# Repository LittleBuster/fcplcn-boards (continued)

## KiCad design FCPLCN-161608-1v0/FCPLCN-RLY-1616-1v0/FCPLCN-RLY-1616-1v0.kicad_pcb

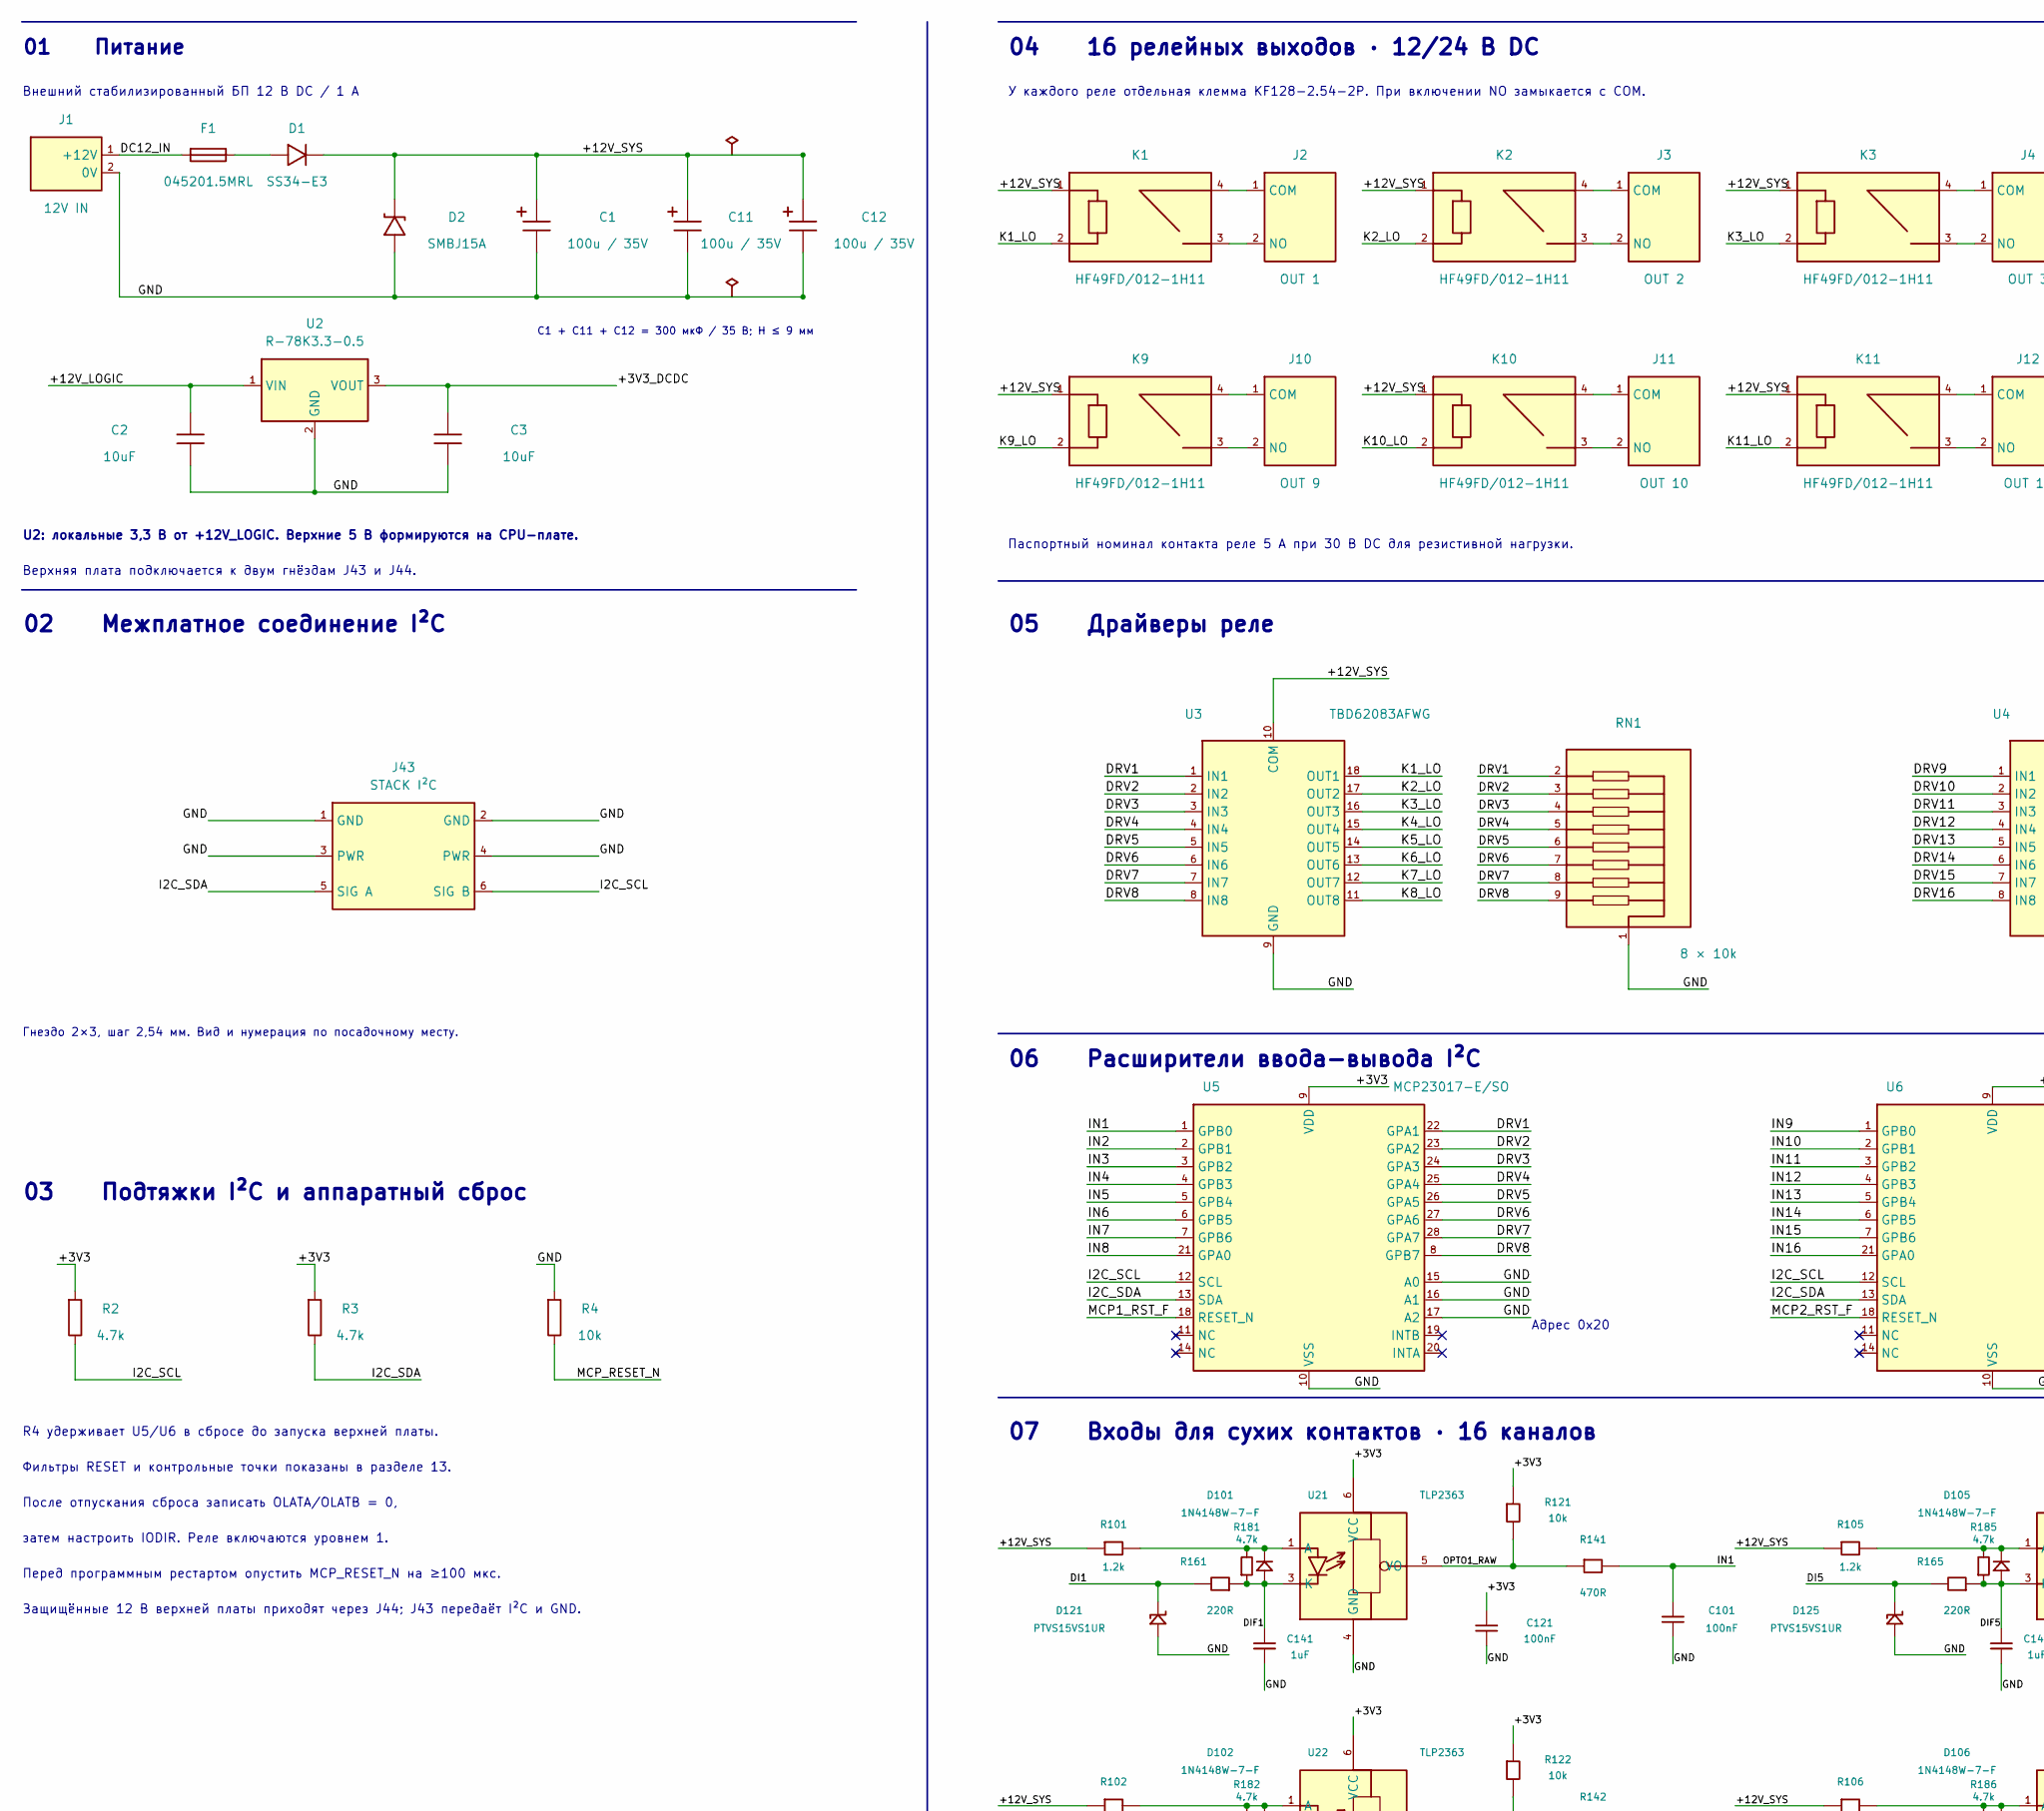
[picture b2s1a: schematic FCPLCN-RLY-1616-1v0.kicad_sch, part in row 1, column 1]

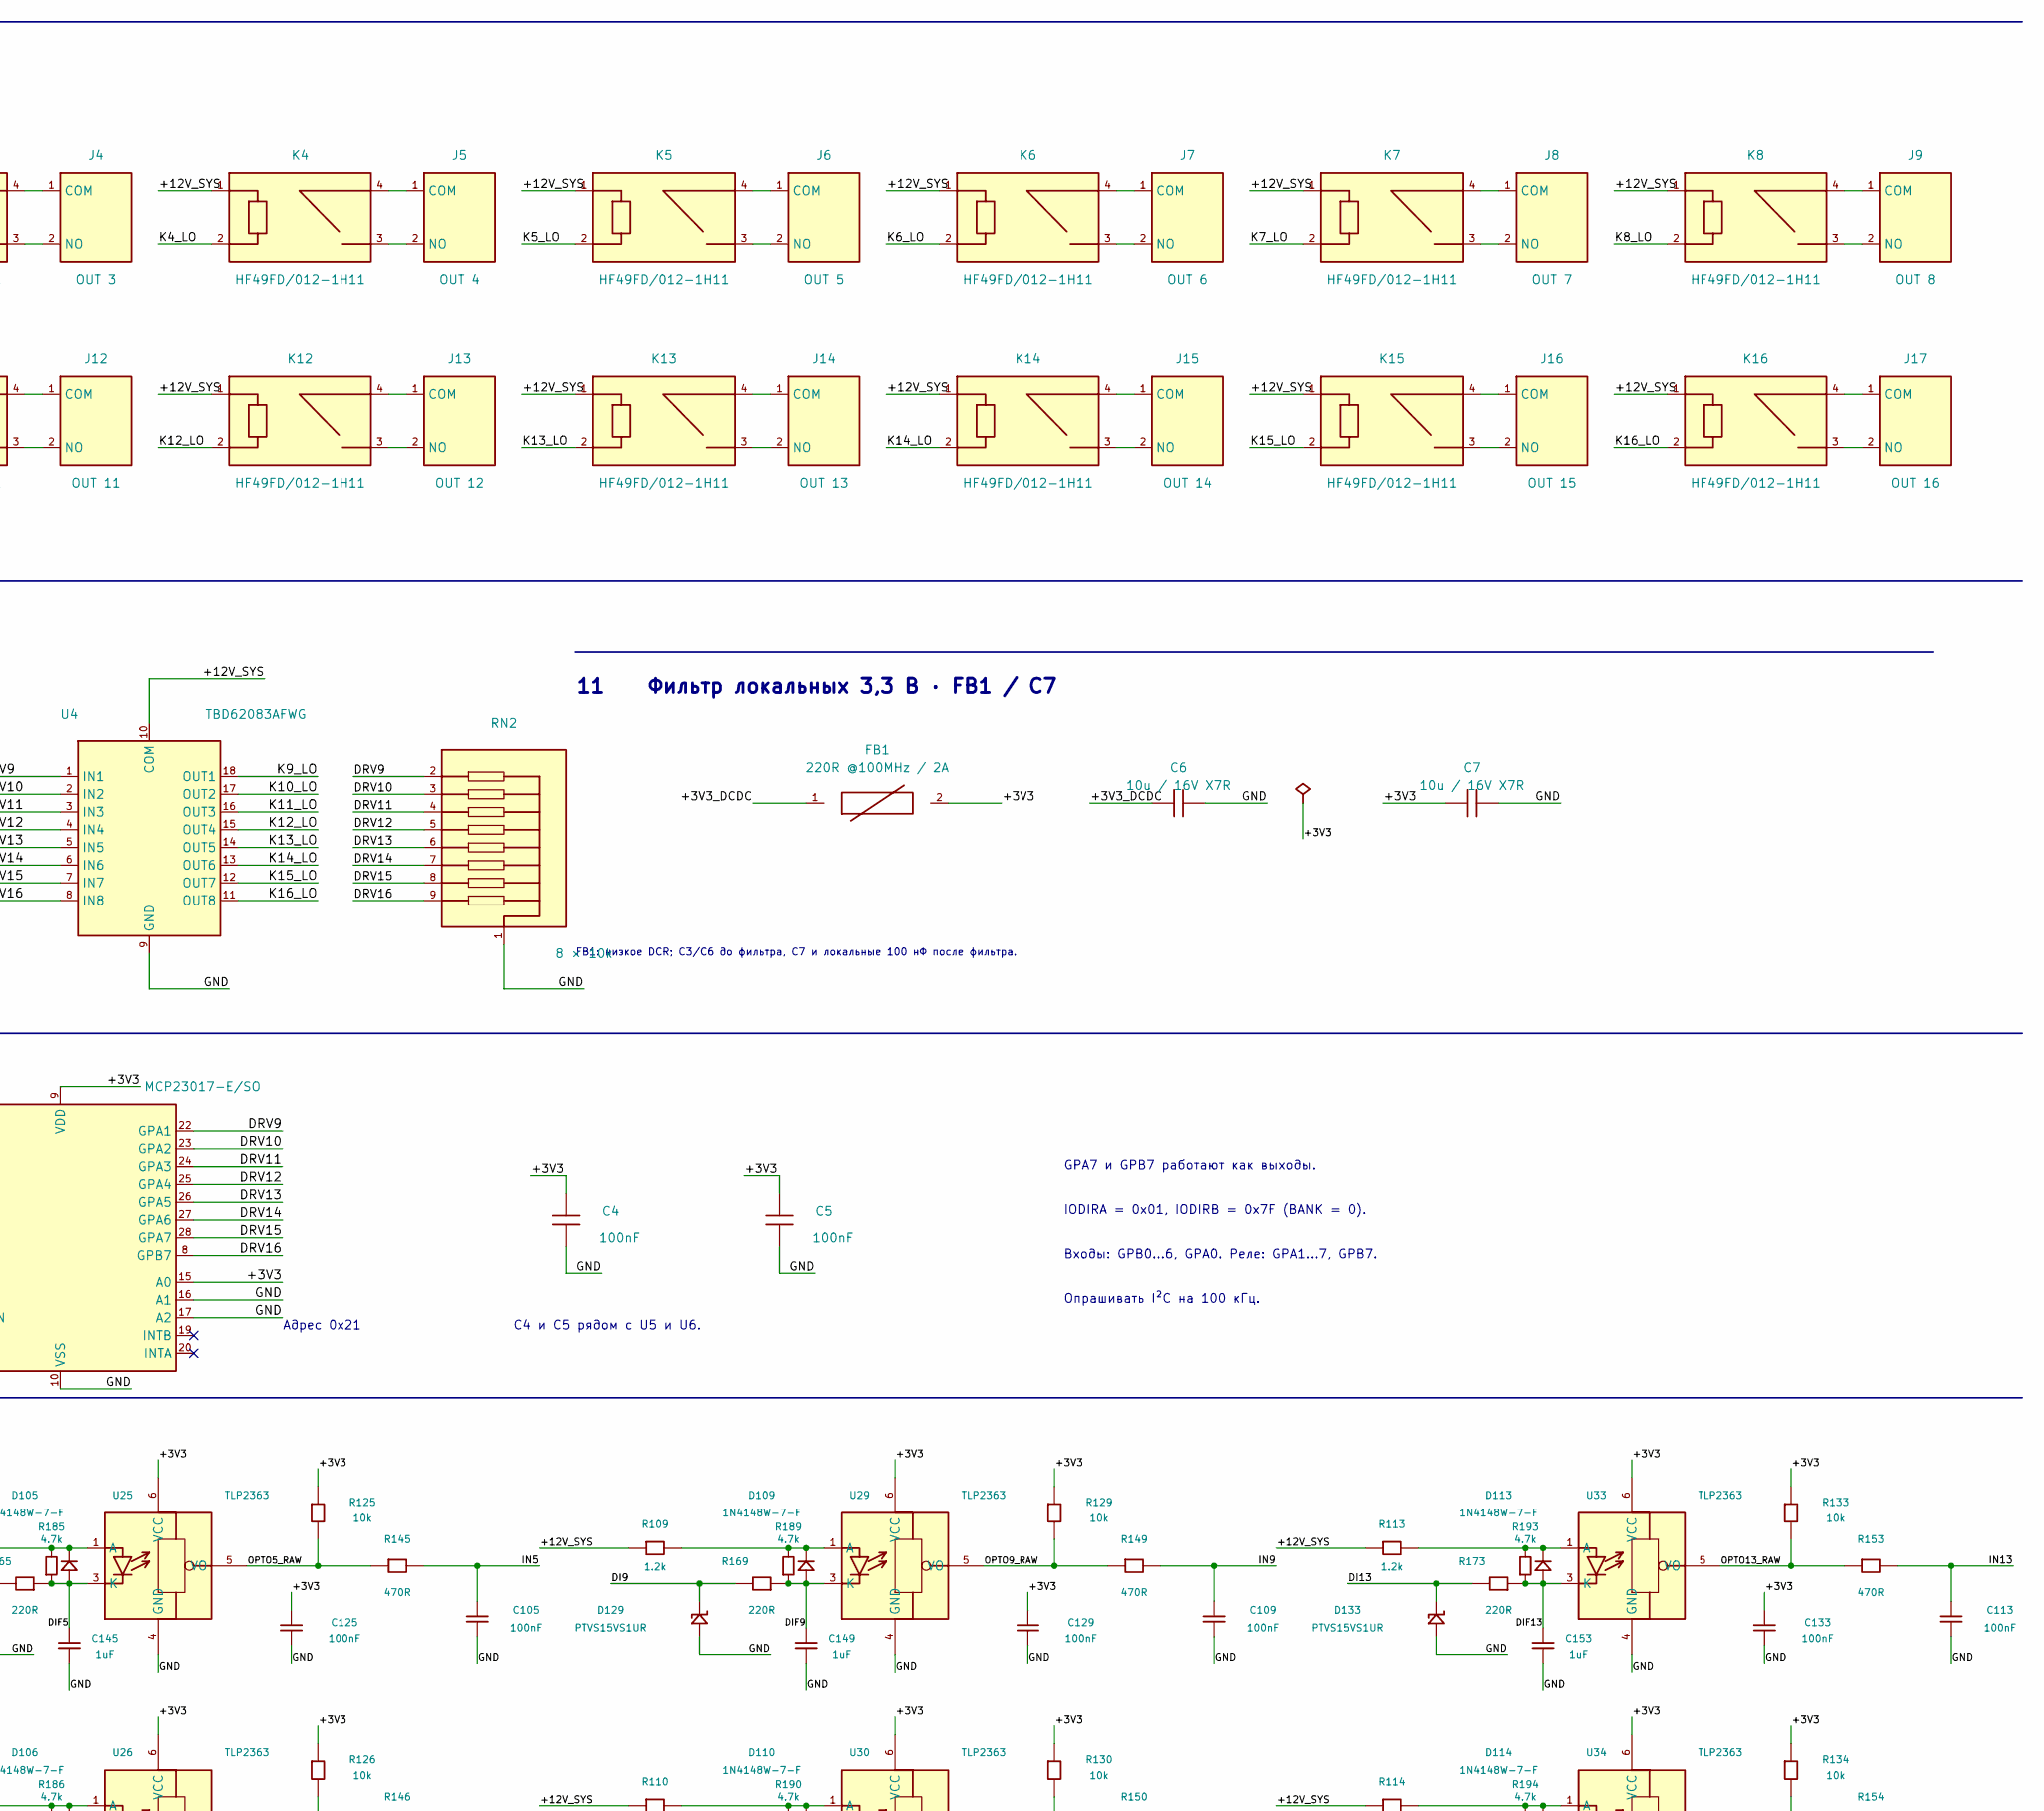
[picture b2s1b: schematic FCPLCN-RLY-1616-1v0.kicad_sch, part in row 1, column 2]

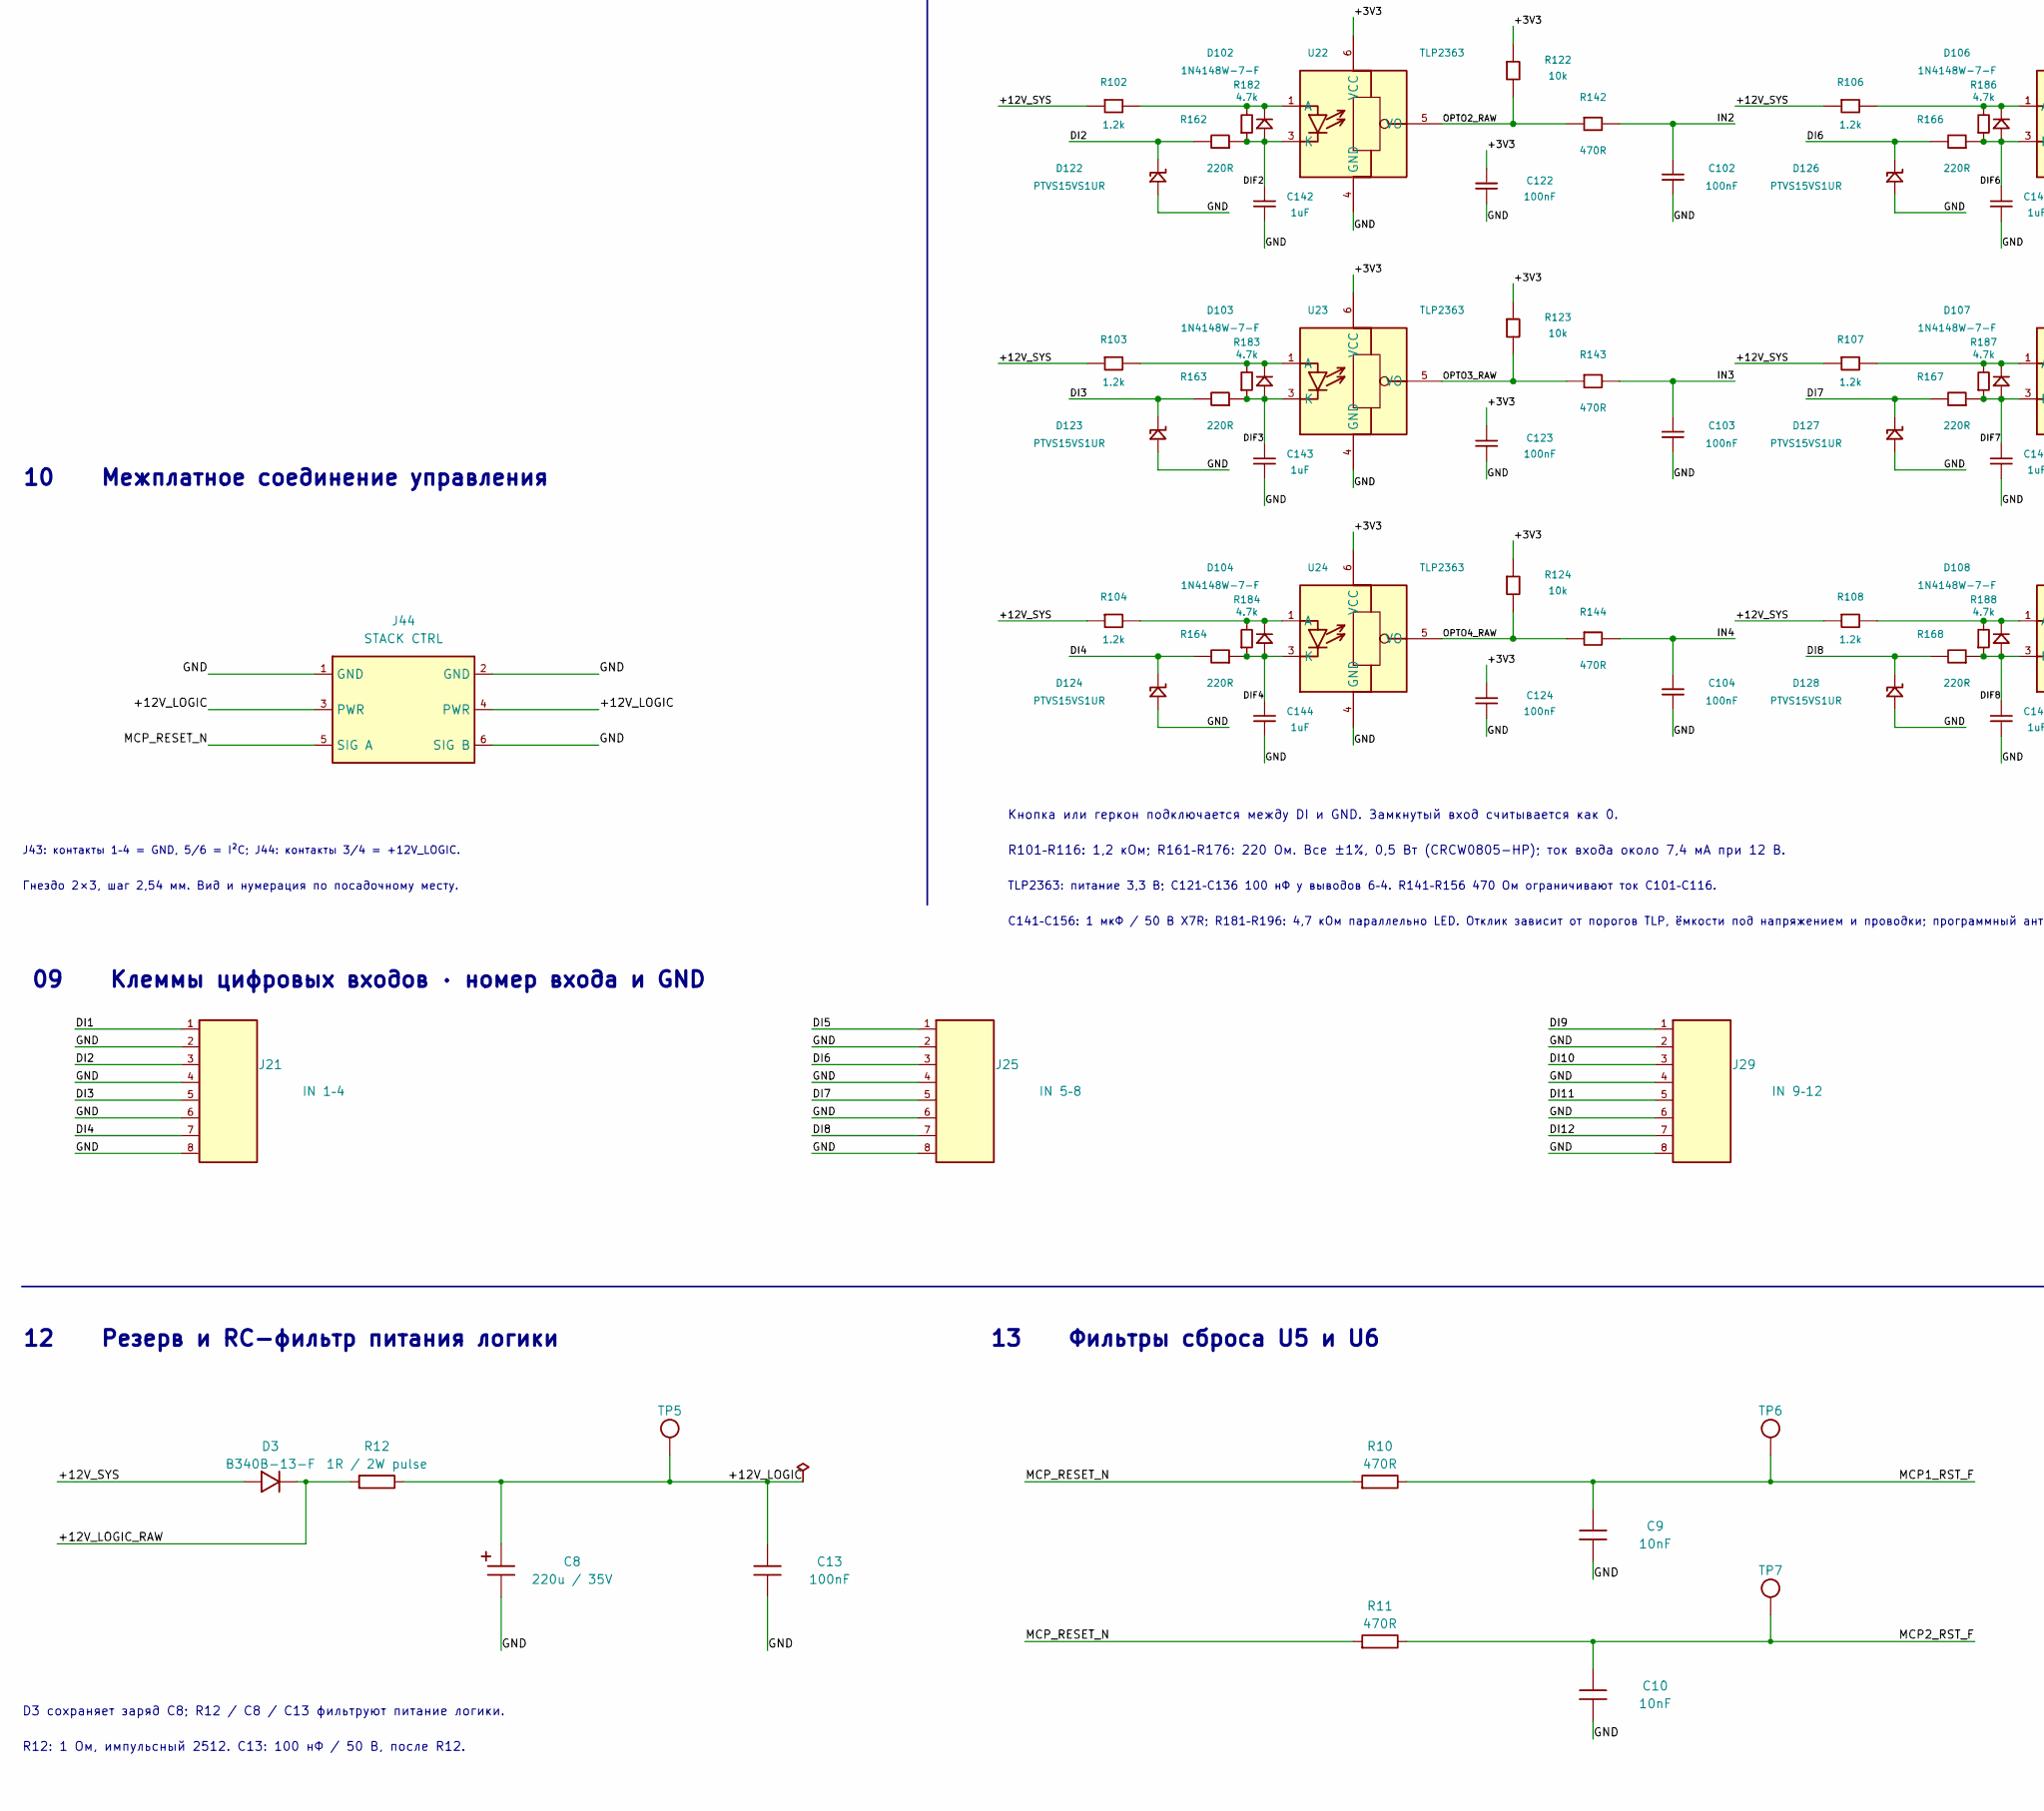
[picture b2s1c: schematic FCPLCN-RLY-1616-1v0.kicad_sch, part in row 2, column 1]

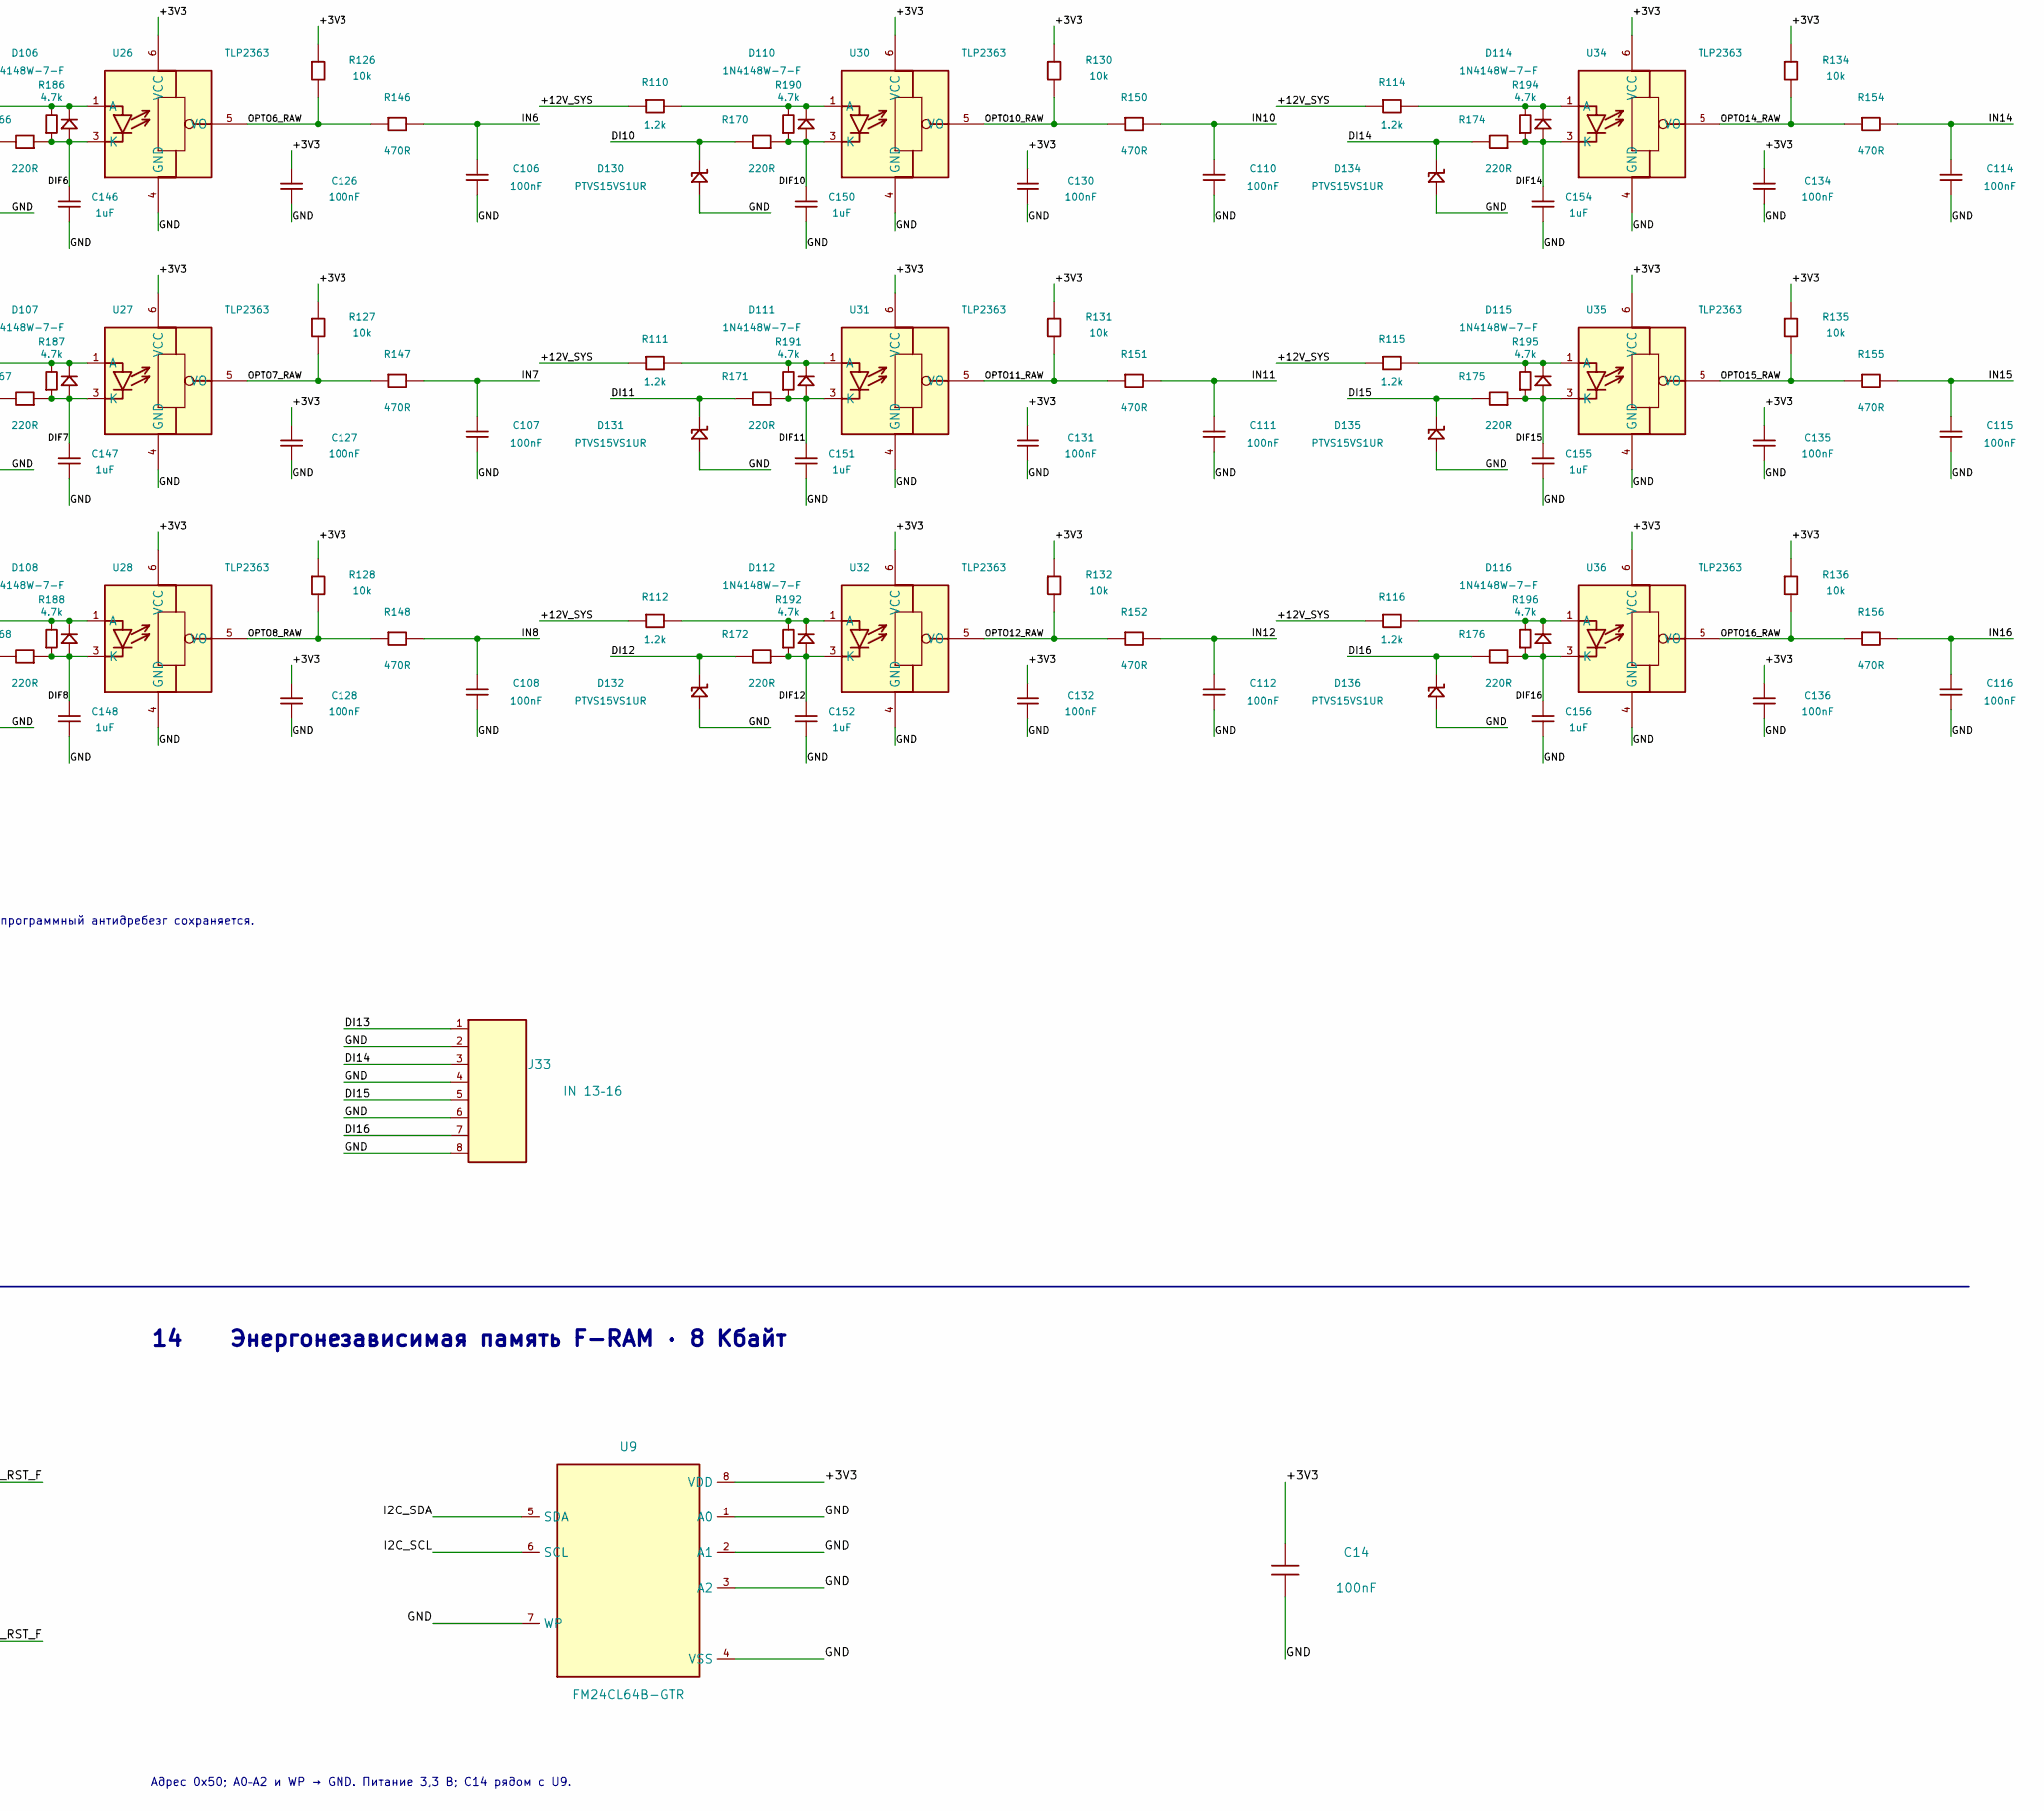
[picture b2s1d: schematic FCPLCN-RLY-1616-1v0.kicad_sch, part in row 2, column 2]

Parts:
C1, C11, C12: 100u / 35V; CP_APAQ_ARHA_D6.3mm_P2.5mm_H9max; Tolerance 20%; MPN 350ARHA101M06X8P00
C2, C3: 10uF; C_1206_3216Metric; Tolerance 10%; Voltage 35 V; MPN C3216X7R1V106K160AC
C4, C5, C14, C101, C102, C103, C104, C105, C106, C107, C108, C109, C110, C111, C112, C113, C114, C115, C116, C121, C122, C123, C124, C125, C126, C127, C128, C129, C130, C131, C132, C133, C134, C135, C136: 100nF; C_0805_2012Metric; Tolerance 10%; Voltage 50 V
C6, C7: 10u / 16V X7R; C_0805_2012Metric
C8: 220u / 35V; CP_Radial_D8.0mm_P3.50mm
C9, C10: 10nF; C_0805_2012Metric; Tolerance 10%; Voltage 50 V
C13: 100nF; C_0805_2012Metric; Voltage 50 V; Tolerance 10%
C141, C142, C143, C144, C145, C146, C147, C148, C149, C150, C151, C152, C153, C154, C155, C156: 1uF; C_0805_2012Metric; Tolerance 10%; Voltage 50 V; MPN C2012X7R1H105K125AB
D1: SS34-E3; D_SMC
D2: SMBJ15A; D_SMB
D3: B340B-13-F; D_SMB
D101, D102, D103, D104, D105, D106, D107, D108, D109, D110, D111, D112, D113, D114, D115, D116: 1N4148W-7-F; D_SOD-123
D121, D122, D123, D124, D125, D126, D127, D128, D129, D130, D131, D132, D133, D134, D135, D136: PTVS15VS1UR; Nexperia_CFP3_SOD-123W
F1: 045201.5MRL; Fuse_Littelfuse-NANO2-451_453; MPN 045201.5MRL
FB1: 220R @100MHz / 2A; L_0805_PowerFilter; MPN BLM21PG221SN1D
J1: 12V IN; KF128-2.54-2P
J2: OUT 1; KF128-2.54-2P
J3: OUT 2; KF128-2.54-2P
J4: OUT 3; KF128-2.54-2P
J5: OUT 4; KF128-2.54-2P
J6: OUT 5; KF128-2.54-2P
J7: OUT 6; KF128-2.54-2P
J8: OUT 7; KF128-2.54-2P
J9: OUT 8; KF128-2.54-2P
J10: OUT 9; KF128-2.54-2P
J11: OUT 10; KF128-2.54-2P
J12: OUT 11; KF128-2.54-2P
J13: OUT 12; KF128-2.54-2P
J14: OUT 13; KF128-2.54-2P
J15: OUT 14; KF128-2.54-2P
J16: OUT 15; KF128-2.54-2P
J17: OUT 16; KF128-2.54-2P
J21: IN 1–4; KF128-2.54-8P
J25: IN 5–8; KF128-2.54-8P
J29: IN 9–12; KF128-2.54-8P
J33: IN 13–16; KF128-2.54-8P
J43: STACK I²C; StackSocket_2x03_P2.54mm; MPN SSW-103-01-L-D
J44: STACK CTRL; StackSocket_2x03_P2.54mm; MPN SSW-103-01-L-D
K1, K2, K3, K4, K5, K6, K7, K8, K9, K10, K11, K12, K13, K14, K15, K16: HF49FD/012-1H11; Relay_SPST_Hongfa_HF49FD-1H11
R2, R3, R181, R182, R183, R184, R185, R186, R187, R188, R189, R190, R191, R192, R193, R194, R195, R196: 4.7k; R_0805_2012Metric; Tolerance 1%
R4, R121, R122, R123, R124, R125, R126, R127, R128, R129, R130, R131, R132, R133, R134, R135, R136: 10k; R_0805_2012Metric; Tolerance 1%
R10, R11, R141, R142, R143, R144, R145, R146, R147, R148, R149, R150, R151, R152, R153, R154, R155, R156: 470R; R_0805_2012Metric; Tolerance 1%
R12: 1R / 2W pulse; R_2512_6332Metric; Tolerance 1%; Voltage_Drop_Design 0.55 V at simultaneous design budget; MPN CRM2512-FX-1R00ELF
R101, R102, R103, R104, R105, R106, R107, R108, R109, R110, R111, R112, R113, R114, R115, R116: 1.2k; R_0805_Wetting; Tolerance 1%; MPN CRCW08051K20FKTAHP
R161, R162, R163, R164, R165, R166, R167, R168, R169, R170, R171, R172, R173, R174, R175, R176: 220R; R_0805_2012Metric; Tolerance 1%; MPN CRCW0805220RFKTAHP
RN1, RN2: 8 × 10k; R_Array_SIP9
TP5, TP6, TP7: TP; TestPoint_Pad_D1.5mm
U2: R-78K3.3-0.5; RECOM_R-78K3.3-0.5_SIP3_P2.54mm; MPN R-78K3.3-0.5
U3, U4: TBD62083AFWG; SOP-18_7.495x11.515mm_P1.27mm
U5, U6: MCP23017-E/SO; SOIC-28W_7.5x17.9mm_P1.27mm
U9: FM24CL64B-GTR; SOIC-8_3.9x4.9mm_P1.27mm; MPN FM24CL64B-GTR
U21, U22, U23, U24, U25, U26, U27, U28, U29, U30, U31, U32, U33, U34, U35, U36: TLP2363; TLP2363_5pin_SO6; MPN TLP2363(TPL,E

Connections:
/+3V3: C4.1, C5.1, C7.1, C14.1, C121.1, C122.1, C123.1, C124.1, C125.1, C126.1, C127.1, C128.1, C129.1, C130.1, C131.1, C132.1, C133.1, C134.1, C135.1, C136.1, FB1.2, R2.1, R3.1, R121.1, R122.1, R123.1, R124.1, R125.1, R126.1, R127.1, R128.1, R129.1, R130.1, R131.1, R132.1, R133.1, R134.1, R135.1, R136.1, U5.9 (VDD), U6.9 (VDD), U6.15 (A0), U9.8 (VDD), U21.6 (VCC), U22.6 (VCC), U23.6 (VCC), U24.6 (VCC), U25.6 (VCC), U26.6 (VCC), U27.6 (VCC), U28.6 (VCC), U29.6 (VCC), U30.6 (VCC), U31.6 (VCC), U32.6 (VCC), U33.6 (VCC), U34.6 (VCC), U35.6 (VCC), U36.6 (VCC)
/+3V3_DCDC: C3.1, C6.1, FB1.1, U2.3 (VOUT)
/+12V_LOGIC: C2.1, C8.1 (+), C13.1, J44.3 (PWR), J44.4 (PWR), R12.2, TP5.1, U2.1 (VIN)
/+12V_LOGIC_RAW: D3.1 (K), R12.1
/+12V_SYS: C1.1 (+), C11.1 (+), C12.1 (+), D1.1 (K), D2.1 (K), D3.2 (A), K1.1 (COIL), K2.1 (COIL), K3.1 (COIL), K4.1 (COIL), K5.1 (COIL), K6.1 (COIL), K7.1 (COIL), K8.1 (COIL), K9.1 (COIL), K10.1 (COIL), K11.1 (COIL), K12.1 (COIL), K13.1 (COIL), K14.1 (COIL), K15.1 (COIL), K16.1 (COIL), R101.1, R102.1, R103.1, R104.1, R105.1, R106.1, R107.1, R108.1, R109.1, R110.1, R111.1, R112.1, R113.1, R114.1, R115.1, R116.1, U3.10 (COM), U4.10 (COM)
/DC12_IN: F1.1, J1.1 (+12V)
/DI1: D121.1 (K), J21.1, R161.2
/DI2: D122.1 (K), J21.3, R162.2
/DI3: D123.1 (K), J21.5, R163.2
/DI4: D124.1 (K), J21.7, R164.2
/DI5: D125.1 (K), J25.1, R165.2
/DI6: D126.1 (K), J25.3, R166.2
/DI7: D127.1 (K), J25.5, R167.2
/DI8: D128.1 (K), J25.7, R168.2
/DI9: D129.1 (K), J29.1, R169.2
/DI10: D130.1 (K), J29.3, R170.2
/DI11: D131.1 (K), J29.5, R171.2
/DI12: D132.1 (K), J29.7, R172.2
/DI13: D133.1 (K), J33.1, R173.2
/DI14: D134.1 (K), J33.3, R174.2
/DI15: D135.1 (K), J33.5, R175.2
/DI16: D136.1 (K), J33.7, R176.2
/DIF1: C141.1, D101.2 (A), R161.1, R181.2, U21.3 (K)
/DIF2: C142.1, D102.2 (A), R162.1, R182.2, U22.3 (K)
/DIF3: C143.1, D103.2 (A), R163.1, R183.2, U23.3 (K)
/DIF4: C144.1, D104.2 (A), R164.1, R184.2, U24.3 (K)
/DIF5: C145.1, D105.2 (A), R165.1, R185.2, U25.3 (K)
/DIF6: C146.1, D106.2 (A), R166.1, R186.2, U26.3 (K)
/DIF7: C147.1, D107.2 (A), R167.1, R187.2, U27.3 (K)
/DIF8: C148.1, D108.2 (A), R168.1, R188.2, U28.3 (K)
/DIF9: C149.1, D109.2 (A), R169.1, R189.2, U29.3 (K)
/DIF10: C150.1, D110.2 (A), R170.1, R190.2, U30.3 (K)
/DIF11: C151.1, D111.2 (A), R171.1, R191.2, U31.3 (K)
/DIF12: C152.1, D112.2 (A), R172.1, R192.2, U32.3 (K)
/DIF13: C153.1, D113.2 (A), R173.1, R193.2, U33.3 (K)
/DIF14: C154.1, D114.2 (A), R174.1, R194.2, U34.3 (K)
/DIF15: C155.1, D115.2 (A), R175.1, R195.2, U35.3 (K)
/DIF16: C156.1, D116.2 (A), R176.1, R196.2, U36.3 (K)
/DRV1: RN1.2, U3.1 (IN1), U5.22 (GPA1)
/DRV2: RN1.3, U3.2 (IN2), U5.23 (GPA2)
/DRV3: RN1.4, U3.3 (IN3), U5.24 (GPA3)
/DRV4: RN1.5, U3.4 (IN4), U5.25 (GPA4)
/DRV5: RN1.6, U3.5 (IN5), U5.26 (GPA5)
/DRV6: RN1.7, U3.6 (IN6), U5.27 (GPA6)
/DRV7: RN1.8, U3.7 (IN7), U5.28 (GPA7)
/DRV8: RN1.9, U3.8 (IN8), U5.8 (GPB7)
/DRV9: RN2.2, U4.1 (IN1), U6.22 (GPA1)
/DRV10: RN2.3, U4.2 (IN2), U6.23 (GPA2)
/DRV11: RN2.4, U4.3 (IN3), U6.24 (GPA3)
/DRV12: RN2.5, U4.4 (IN4), U6.25 (GPA4)
/DRV13: RN2.6, U4.5 (IN5), U6.26 (GPA5)
/DRV14: RN2.7, U4.6 (IN6), U6.27 (GPA6)
/DRV15: RN2.8, U4.7 (IN7), U6.28 (GPA7)
/DRV16: RN2.9, U4.8 (IN8), U6.8 (GPB7)
/GND: C1.2 (-), C2.2, C3.2, C4.2, C5.2, C6.2, C7.2, C8.2 (-), C9.2, C10.2, C11.2 (-), C12.2 (-), C13.2, C14.2, C101.2, C102.2, C103.2, C104.2, C105.2, C106.2, C107.2, C108.2, C109.2, C110.2, C111.2, C112.2, C113.2, C114.2, C115.2, C116.2, C121.2, C122.2, C123.2, C124.2, C125.2, C126.2, C127.2, C128.2, C129.2, C130.2, C131.2, C132.2, C133.2, C134.2, C135.2, C136.2, C141.2, C142.2, C143.2, C144.2, C145.2, C146.2, C147.2, C148.2, C149.2, C150.2, C151.2, C152.2, C153.2, C154.2, C155.2, C156.2, D2.2 (A), D121.2 (A), D122.2 (A), D123.2 (A), D124.2 (A), D125.2 (A), D126.2 (A), D127.2 (A), D128.2 (A), D129.2 (A), D130.2 (A), D131.2 (A), D132.2 (A), D133.2 (A), D134.2 (A), D135.2 (A), D136.2 (A), J1.2 (0V), J21.2, J21.4, J21.6, J21.8, J25.2, J25.4, J25.6, J25.8, J29.2, J29.4, J29.6, J29.8, J33.2, J33.4, J33.6, J33.8, J43.1 (GND), J43.2 (GND), J43.3 (PWR), J43.4 (PWR), J44.1 (GND), J44.2 (GND), J44.6 (SIG B), R4.1, RN1.1 (COM), RN2.1 (COM), U2.2 (GND), U3.9 (GND), U4.9 (GND), U5.10 (VSS), U5.15 (A0), U5.16 (A1), U5.17 (A2), U6.10 (VSS), U6.16 (A1), U6.17 (A2), U9.1 (A0), U9.2 (A1), U9.3 (A2), U9.4 (VSS), U9.7 (WP), U21.4 (GND), U22.4 (GND), U23.4 (GND), U24.4 (GND), U25.4 (GND), U26.4 (GND), U27.4 (GND), U28.4 (GND), U29.4 (GND), U30.4 (GND), U31.4 (GND), U32.4 (GND), U33.4 (GND), U34.4 (GND), U35.4 (GND), U36.4 (GND)
/I2C_SCL: J43.6 (SIG B), R2.2, U5.12 (SCL), U6.12 (SCL), U9.6 (SCL)
/I2C_SDA: J43.5 (SIG A), R3.2, U5.13 (SDA), U6.13 (SDA), U9.5 (SDA)
/IN1: C101.1, R141.2, U5.1 (GPB0)
/IN2: C102.1, R142.2, U5.2 (GPB1)
/IN3: C103.1, R143.2, U5.3 (GPB2)
/IN4: C104.1, R144.2, U5.4 (GPB3)
/IN5: C105.1, R145.2, U5.5 (GPB4)
/IN6: C106.1, R146.2, U5.6 (GPB5)
/IN7: C107.1, R147.2, U5.7 (GPB6)
/IN8: C108.1, R148.2, U5.21 (GPA0)
/IN9: C109.1, R149.2, U6.1 (GPB0)
/IN10: C110.1, R150.2, U6.2 (GPB1)
/IN11: C111.1, R151.2, U6.3 (GPB2)
/IN12: C112.1, R152.2, U6.4 (GPB3)
/IN13: C113.1, R153.2, U6.5 (GPB4)
/IN14: C114.1, R154.2, U6.6 (GPB5)
/IN15: C115.1, R155.2, U6.7 (GPB6)
/IN16: C116.1, R156.2, U6.21 (GPA0)
/K1_LO: K1.2 (COIL), U3.18 (OUT1)
/K2_LO: K2.2 (COIL), U3.17 (OUT2)
/K3_LO: K3.2 (COIL), U3.16 (OUT3)
/K4_LO: K4.2 (COIL), U3.15 (OUT4)
/K5_LO: K5.2 (COIL), U3.14 (OUT5)
/K6_LO: K6.2 (COIL), U3.13 (OUT6)
/K7_LO: K7.2 (COIL), U3.12 (OUT7)
/K8_LO: K8.2 (COIL), U3.11 (OUT8)
/K9_LO: K9.2 (COIL), U4.18 (OUT1)
/K10_LO: K10.2 (COIL), U4.17 (OUT2)
/K11_LO: K11.2 (COIL), U4.16 (OUT3)
/K12_LO: K12.2 (COIL), U4.15 (OUT4)
/K13_LO: K13.2 (COIL), U4.14 (OUT5)
/K14_LO: K14.2 (COIL), U4.13 (OUT6)
/K15_LO: K15.2 (COIL), U4.12 (OUT7)
/K16_LO: K16.2 (COIL), U4.11 (OUT8)
/MCP1_RST_F: C9.1, R10.2, TP6.1, U5.18 (RESET_N)
/MCP2_RST_F: C10.1, R11.2, TP7.1, U6.18 (RESET_N)
/MCP_RESET_N: J44.5 (SIG A), R4.2, R10.1, R11.1
/OPTO1_RAW: R121.2, R141.1, U21.5 (VO)
/OPTO2_RAW: R122.2, R142.1, U22.5 (VO)
/OPTO3_RAW: R123.2, R143.1, U23.5 (VO)
/OPTO4_RAW: R124.2, R144.1, U24.5 (VO)
/OPTO5_RAW: R125.2, R145.1, U25.5 (VO)
/OPTO6_RAW: R126.2, R146.1, U26.5 (VO)
/OPTO7_RAW: R127.2, R147.1, U27.5 (VO)
/OPTO8_RAW: R128.2, R148.1, U28.5 (VO)
/OPTO9_RAW: R129.2, R149.1, U29.5 (VO)
/OPTO10_RAW: R130.2, R150.1, U30.5 (VO)
/OPTO11_RAW: R131.2, R151.1, U31.5 (VO)
/OPTO12_RAW: R132.2, R152.1, U32.5 (VO)
/OPTO13_RAW: R133.2, R153.1, U33.5 (VO)
/OPTO14_RAW: R134.2, R154.1, U34.5 (VO)
/OPTO15_RAW: R135.2, R155.1, U35.5 (VO)
/OPTO16_RAW: R136.2, R156.1, U36.5 (VO)
unnamed: D1.2 (A), F1.2
unnamed: D101.1 (K), R101.2, R181.1, U21.1 (A)
unnamed: D102.1 (K), R102.2, R182.1, U22.1 (A)
unnamed: D103.1 (K), R103.2, R183.1, U23.1 (A)
unnamed: D104.1 (K), R104.2, R184.1, U24.1 (A)
unnamed: D105.1 (K), R105.2, R185.1, U25.1 (A)
unnamed: D106.1 (K), R106.2, R186.1, U26.1 (A)
unnamed: D107.1 (K), R107.2, R187.1, U27.1 (A)
unnamed: D108.1 (K), R108.2, R188.1, U28.1 (A)
unnamed: D109.1 (K), R109.2, R189.1, U29.1 (A)
unnamed: D110.1 (K), R110.2, R190.1, U30.1 (A)
unnamed: D111.1 (K), R111.2, R191.1, U31.1 (A)
unnamed: D112.1 (K), R112.2, R192.1, U32.1 (A)
unnamed: D113.1 (K), R113.2, R193.1, U33.1 (A)
unnamed: D114.1 (K), R114.2, R194.1, U34.1 (A)
unnamed: D115.1 (K), R115.2, R195.1, U35.1 (A)
unnamed: D116.1 (K), R116.2, R196.1, U36.1 (A)
unnamed: J2.1 (COM), K1.4 (COM)
unnamed: J2.2 (NO), K1.3 (NO)
unnamed: J3.1 (COM), K2.4 (COM)
unnamed: J3.2 (NO), K2.3 (NO)
unnamed: J4.1 (COM), K3.4 (COM)
unnamed: J4.2 (NO), K3.3 (NO)
unnamed: J5.1 (COM), K4.4 (COM)
unnamed: J5.2 (NO), K4.3 (NO)
unnamed: J6.1 (COM), K5.4 (COM)
unnamed: J6.2 (NO), K5.3 (NO)
unnamed: J7.1 (COM), K6.4 (COM)
unnamed: J7.2 (NO), K6.3 (NO)
unnamed: J8.1 (COM), K7.4 (COM)
unnamed: J8.2 (NO), K7.3 (NO)
unnamed: J9.1 (COM), K8.4 (COM)
unnamed: J9.2 (NO), K8.3 (NO)
unnamed: J10.1 (COM), K9.4 (COM)
unnamed: J10.2 (NO), K9.3 (NO)
unnamed: J11.1 (COM), K10.4 (COM)
unnamed: J11.2 (NO), K10.3 (NO)
unnamed: J12.1 (COM), K11.4 (COM)
unnamed: J12.2 (NO), K11.3 (NO)
unnamed: J13.1 (COM), K12.4 (COM)
unnamed: J13.2 (NO), K12.3 (NO)
unnamed: J14.1 (COM), K13.4 (COM)
unnamed: J14.2 (NO), K13.3 (NO)
unnamed: J15.1 (COM), K14.4 (COM)
unnamed: J15.2 (NO), K14.3 (NO)
unnamed: J16.1 (COM), K15.4 (COM)
unnamed: J16.2 (NO), K15.3 (NO)
unnamed: J17.1 (COM), K16.4 (COM)
unnamed: J17.2 (NO), K16.3 (NO)

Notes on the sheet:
07 Входы для сухих контактов · 16 каналов
01 Питание
Внешний стабилизированный БП 12 В DC / 1 А
U2: локальные 3,3 В от +12V_LOGIC. Верхние 5 В формируются на CPU-плате.
Верхняя плата подключается к двум гнёздам J43 и J44.
03 Подтяжки I²C и аппаратный сброс
R4 удерживает U5/U6 в сбросе до запуска верхней платы.
Фильтры RESET и контрольные точки показаны в разделе 13.
После отпускания сброса записать OLATA/OLATB = 0,
затем настроить IODIR. Реле включаются уровнем 1.
Перед программным рестартом опустить MCP_RESET_N на ≥100 мкс.
Защищённые 12 В верхней платы приходят через J44; J43 передаёт I²C и GND.
04 16 релейных выходов · 12/24 В DC
У каждого реле отдельная клемма KF128-2.54-2P. При включении NO замыкается с COM.
Паспортный номинал контакта реле 5 А при 30 В DC для резистивной нагрузки.
05 Драйверы реле
06 Расширители ввода-вывода I²C
Адрес 0x20
Адрес 0x21
C4 и C5 рядом с U5 и U6.
GPA7 и GPB7 работают как выходы.
IODIRA = 0x01, IODIRB = 0x7F (BANK = 0).
Входы: GPB0…6, GPA0. Реле: GPA1…7, GPB7.
Опрашивать I²C на 100 кГц.
Кнопка или геркон подключается между DI и GND. Замкнутый вход считывается как 0.
R101–R116: 1,2 кОм; R161–R176: 220 Ом. Все ±1%, 0,5 Вт (CRCW0805-HP); ток входа около 7,4 мА при 12 В.
09 Клеммы цифровых входов · номер входа и GND
11 Фильтр локальных 3,3 В · FB1 / C7
12 Резерв и RC-фильтр питания логики
D3 сохраняет заряд C8; R12 / C8 / C13 фильтруют питание логики.
R12: 1 Ом, импульсный 2512. C13: 100 нФ / 50 В, после R12.
13 Фильтры сброса U5 и U6
02 Межплатное соединение I²C
Гнездо 2×3, шаг 2,54 мм. Вид и нумерация по посадочному месту.
10 Межплатное соединение управления
C1 + C11 + C12 = 300 мкФ / 35 В; H ≤ 9 мм
J43: контакты 1–4 = GND, 5/6 = I²C; J44: контакты 3/4 = +12V_LOGIC.
14 Энергонезависимая память F-RAM · 8 Кбайт
Адрес 0x50; A0–A2 и WP → GND. Питание 3,3 В; C14 рядом с U9.
TLP2363: питание 3,3 В; C121–C136 100 нФ у выводов 6–4. R141–R156 470 Ом ограничивают ток C101–C116.
